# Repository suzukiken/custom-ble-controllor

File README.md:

# Xiao BLE Controller

Seeed XIAO 向けのファーム／周辺ツール集です。**スタック（どの MCU・どのランタイムか）で場所が分かれています。**

## ファームの場所（まずここ）

| 種類 | 置き場 | 例 |
| --- | --- | --- |
| **ZMK（XIAO nRF52840）** | リポジトリ直下 `config/` + `boards/shields/` | `sleep_xiao`, `onekey_xiao`, … |
| **Arduino（XIAO RP2040）** | [`arduino/xiao-rp2040/`](arduino/xiao-rp2040/) | `virtual-finger`（nRF を押す仮想指） |

積み重ね（nRF + RP2040）のペア:

| ZMK shield（nRF・電池） | RP2040 finger（USB） |
| --- | --- |
| `sleep_xiao`（deep sleep **あり**） | [`virtual-finger`](arduino/xiao-rp2040/virtual-finger/)（D0） |
| `sleep_xiao_pi`（同上 + Pi/BlueZ 向け BLE） | 同じ |
| `awake_xiao`（deep sleep **なし**） | 同じ |
| `awake_xiao_pi`（awake + Pi/BlueZ 向け BLE） | 同じ |

RP2040: **D0** を約5分おきにパルス。nRF は `time: …, power=…, mode=…` を打つ。

### スリープあり／なし比較（手元の機材向け）

公平に見るには **打鍵周期を同じにして sleep だけ変える**。

| 役割 | nRF ファーム | RP2040 | ホスト例 | 見るもの |
| --- | --- | --- | --- | --- |
| A | `sleep_xiao`（deep sleep **あり**） | `virtual-finger` | iPad | 持ち時間 |
| B | `awake_xiao`（deep sleep **なし**） | `virtual-finger` | iPhone | 持ち時間 |
| C | `sleep_xiao`（deep sleep あり） | **なし**（接続だけ） | Mac | ベースライン |

- 電池3本は満充電から開始。nRF=LiPo / RP2040=USB。**GND + D0** を共有。
- ホストはどれも近く・同じ部屋に固定（距離差で再送が増えると壊れる）。
- 画面は自動ロック「しない」、試験中は寝かさない。
- Notes 等に約5分ごと `time: …, power=…, mode=sleep|awake` が出る。
- 切れ時刻か、最後の `time:` で比較。A≪B なら sleep が効いている。A≈B なら接続維持が支配的。
- C が A より大幅に長いなら「5分打鍵＋起床」のコストが見える。

詳細は [`arduino/README.md`](arduino/README.md)。ZMK は user-config の都合でルートに残しています。

---

## ZMK user config（nRF52840）

Board は `xiao_ble//zmk`。ZMK 本体は [`config/west.yml`](config/west.yml) で commit `268b1b1e82150460f00fd701bcd08583d5c75d29` に固定しています。

## Shield 一覧

| Shield | ハードウェア | ピン | キーマップ / センサ |
| --- | --- | --- | --- |
| `onekey_xiao` | `one-key` | D0 ↔ GND | `SPACE` |
| `key_xiao` | `main-board` + `key-board`（PH 2） | D0 ↔ GND | `SPACE` |
| `encoder_xiao` | `main-board` + `encoder-board`（PH 3） | D1=A, D2=B, GND=C | 回転: `C_VOL_UP` / `C_VOL_DN` |
| `push_encoder_xiao` | `main-board` + `push-encoder-board`（PH 4） | D7=A, D6=B, D5=SW, GND=C | Push: `C_MUTE` / 回転: 音量 |
| `fourway_xiao` | `main-board-8` + `4way-re-board`（8ピン, RKJXT1F42001） | 下表 | 十字・Enter・音量 |
| `key_encoder_xiao` | Xiao + keyswitch + encoder 一体 | D0=SW / D1=A, D2=B, GND | `SPACE` + 方向キー上下 |
| `rkjxt_xiao` | Xiao + RKJXT1F42001 一体 | 下表 | 十字・Enter・音量 |
| `sleep_xiao` | 仮想指 + deep sleep あり | D0 ↔ RP2040 | D0=status |
| `sleep_xiao_pi` | `sleep_xiao` + Raspberry Pi/BlueZ 向け BLE | 同上 | 2M PHY 無効など |
| `awake_xiao` | 仮想指 + deep sleep **なし** | D0 ↔ RP2040 | D0=status |
| `awake_xiao_pi` | `awake_xiao` + Pi/BlueZ 向け BLE | 同上 | 接続切り分け用 |
| `drain_xiao` | **電池消費最大化**（充電電流計測の前処理） | （キー不要） | RGB+CPU+HID spam |
| `powerbtn_xiao` | 電源ボタン（ZMK Soft Off） | D0 ↔ GND | 3秒長押しで System OFF / 押して起動 |

BLE 名はそれぞれ `OneKey Xiao` / `Key Xiao` / `Encoder Xiao` / `PushEnc Xiao` / `Fourway Xiao` / `KeyEnc Xiao` / `Rkjxt Xiao` / `Sleep Xiao` / `Sleep Pi Xiao` / `Awake Xiao` / `Awake Pi Xiao` / `Drain Xiao` / `PowerBtn Xiao` です（ZMK の上限は15文字）。

status の周期は nRF 側ではなく **RP2040**（既定 5 分）が決めます。

共通設定（各 `config/*.conf`）:

- `CONFIG_ZMK_BLE=y` / `CONFIG_ZMK_USB=n`
- `sleep_xiao`: `CONFIG_ZMK_SLEEP=y` / `CONFIG_ZMK_IDLE_SLEEP_TIMEOUT=20000`（status 打鍵後に寝る余裕）。`powerbtn_xiao` と `awake_xiao` は `CONFIG_ZMK_SLEEP=n`
- エンコーダ付きは `CONFIG_EC11=y`

## 配線

### onekey_xiao / key_xiao

```text
XIAO D0 ----[ switch ]---- XIAO GND
```

`zmk,kscan-gpio-direct`、`GPIO_ACTIVE_LOW | GPIO_PULL_UP`。

### encoder_xiao

```text
XIAO D1 ---- Encoder A
XIAO D2 ---- Encoder B
XIAO GND --- Encoder C
```

キー入力は使わず（overlay 上の D10 は未使用スタブ）、回転のみ。

### key_encoder_xiao

Xiao・キースイッチ・ロータリーエンコーダ（プッシュなし）を1枚に載せた構成です。

```text
XIAO D0  ---- keyswitch pin1
XIAO GND ---- keyswitch pin2

XIAO D1  ---- encoder pin1 (A)
XIAO D2  ---- encoder pin3 (B)
XIAO GND ---- encoder pin2 (C)
```

キーは `SPACE`、回転は方向キー Up/Down です。

### push_encoder_xiao

```text
XIAO D7 ---- Encoder A
XIAO D6 ---- Encoder B
XIAO D5 ---- SW (Push)
XIAO GND --- Encoder C
```

### fourway_xiao（RKJXT1F42001）

```text
XIAO D4 ---- A      → UP
XIAO D0 ---- B      → RIGHT
XIAO D2 ---- C      → DOWN
XIAO D3 ---- D      → LEFT
XIAO D5 ---- Push   → ENTER
XIAO D6 ---- Encoder A
XIAO D1 ---- Encoder B
XIAO GND --- GND (Com / ECom)
```

keymap の並びは A, B, C, D, Push。回転は `C_VOL_UP` / `C_VOL_DN`（`steps = 20`）。

### rkjxt_xiao

Xiao と RKJXT1F42001 を1枚に載せた構成です。

```text
XIAO D4 ---- A      → UP
XIAO D0 ---- B      → RIGHT
XIAO D2 ---- C      → DOWN
XIAO D3 ---- D      → LEFT
XIAO D5 ---- Push   → (無効 / 方向と同時導通のため)
XIAO D6 ---- EA (Encoder A)
XIAO D1 ---- EB (Encoder B)
XIAO GND --- GND
```

keymap の並びは A, B, C, D, Push。回転は音量 Up/Down（`steps = 20`）。

RKJXT1F42001 は方向入力時に Push も同時に落ちるため、`rkjxt_xiao` では Push を `&none` にしています（Enter が乗らないようにするため）。中央プッシュが必要なら別途相談してください。

### powerbtn_xiao

```text
XIAO D0 ----[ switch ]---- XIAO GND
```

`zmk,kscan-gpio-direct`。短押しではキーは出ず、3秒長押しで Soft Off（後述）。

### sleep_xiao / awake_xiao（仮想指 + status）

目的は「BLE 接続したまま、約5分に1回 status 行を打つ」ときの持ち時間の見積もりです。`sleep_xiao` は deep sleep あり、`awake_xiao` はなし。

```text
nRF D0 ---- RP2040 D0   (status trigger, ~5min)
nRF GND --- RP2040 GND
```

- D0: keymap は `&none`。`soak_status` が `time: …, power=…, mode=…` + Enter を打つ
- `sleep_xiao`: 入力後 **20秒** でスリープ（status 打鍵が終わる余裕）
- status 周期は **RP2040** 側（既定 5 分）。deep sleep 中でも D0 で起きて送信できる

#### 実験のやり方

1. LiPo を nRF の BAT に接続し、この uf2 を書く
2. ホストと `Sleep Xiao` / `Awake Xiao` をペアリングし、Notes 等を開く
3. RP2040 を積み、**GND + D0** を共有（3V3/5V/BAT は繋がない）。RP2040 は USB 電源
4. 約5分ごとに Notes に status 行が出ることを確認し、電池切れまで測る

見積もりの目安: `稼働時間 = 満充電から不能になるまでの時間`。最後の `time:` でも比較できます。

### sleep_xiao_pi（Raspberry Pi / BlueZ 向け）

`sleep_xiao` と同じ打鍵・スリープ構成で、**BLE だけ** Linux（特に Raspberry Pi の BlueZ）向けに変えています。

ログに `le-connection-abort-by-local` と `Connected: yes`/`no` の高速点滅が出る場合、多くは次のどちらかです。

1. **Pi 側がリンクを切っている**（2M PHY 交渉や SMP/ボンディング不整合で BlueZ が abort）
2. **片方だけの古いボンド**（iPhone 等とペアした鍵が残り、Pi が同じアドレスに古い鍵で接続しようとして失敗→再試行ループ）

`sleep_xiao_pi` では主に次を入れています。

- `CONFIG_ZMK_BLE_EXPERIMENTAL_CONN=y` / `CONFIG_BT_CTLR_PHY_2M=n`（2M PHY 無効）
- ボンド上書き許可（再ペアしやすくする）
- `CONFIG_BT_GATT_ENFORCE_SUBSCRIPTION=n`
- idle sleep を **10分**（virtual-finger の5分より長くする）。あわせて idle も5分に延長
- 送信出力 `CONFIG_BT_CTLR_TX_PWR_PLUS_8=y`

初回は両方きれいにしてからペアしてください。

1. nRF にいったん `settings_reset` を書き、すぐ `sleep_xiao_pi` を書き直す
2. Pi: `bluetoothctl remove <addr>`（該当デバイス）、必要なら `sudo systemctl restart bluetooth`
3. デバイスを起こした状態（D0 パルス後〜60秒以内）で次を実行

```text
agent off
agent NoInputNoOutput
default-agent
scan on
pair <addr>
trust <addr>
connect <addr>
```

**重要:** デスクトップ GUI に「Enter Code 2314134」のような表示が出ることがあります。これは「キーボードでパスコードを打て」という意味で、数字キーの無い本機では入力できません。**GUI のダイアログはキャンセル**し、上記のとおり `agent NoInputNoOutput` の bluetoothctl だけでペアしてください（Just Works）。GUI エージェントが割り込むと失敗しやすいです。

#### つながらないときの切り分け

ログの `Connected: yes`/`no` 連打 + `le-connection-abort-by-local` は、だいたい次の合成です。

1. **ペア未完了／壊れたボンド**（GUI パスコードをキャンセルしたあとに特に多い。`trust` だけでは足りない）
2. **BlueZ × ZMK HID** の相性（2M PHY・認証。ファーム側は 2M 無効などを入れ済み）
3. **deep sleep**（広告が止まる／再接続のたびに同じ失敗を繰り返す）

先に **`awake_xiao_pi`（BLE名 `Awake Pi Xiao`）** でペアを試してください。deep sleep なし・同じ BLE 対策です。

- `awake_xiao_pi` で安定する → 問題は主に sleep／再接続。そのボンドのまま `sleep_xiao_pi` へ載せ替えを検討
- `awake_xiao_pi` でも同じ → deep sleep ではなく **Pi/BlueZ 側**（ボンド掃除・agent・場合によって BT ドングル／OS）が本丸

そのとき `info <addr>` で `Paired: yes` か、できれば `sudo btmon` の切断理由（Authentication / Timeout 等）を見ると次が決まります。

## virtual-finger（Arduino RP2040）

置き場: [`arduino/xiao-rp2040/virtual-finger/`](arduino/xiao-rp2040/virtual-finger/)

| ピン | 周期（既定） | nRF 側の意味 |
| --- | --- | --- |
| `D0` | 5分 | status トリガ（`soak_status`） |

**1.5秒** LOW パルス（deep sleep 起床＋スキャン検出用）。パルス時は赤 LED。起動後約15秒で最初の status が出ます。

GitHub Actions [`Build Arduino RP2040 virtual-finger`](.github/workflows/build-arduino-rp2040-virtual-finger.yml) が UF2 を出します。

1. Actions の Artifacts から `arduino-rp2040-virtual-finger` をダウンロード
2. XIAO RP2040 で **B を押しながら R**（または B 押しながら挿す）→ `RPI-RP2` ドライブ
3. `xiao-rp2040-virtual-finger.uf2` をドラッグ&ドロップ

周期は `INTERVAL_MS` で変更できます。

## drain_xiao（電池を早く減らす・充電計測の前処理）

40mAh などで **半分付近まで落としてから充電電流を測る**ための、消費最大化ファームです。

| 項目 | 内容 |
| --- | --- |
| BLE 名 | `Drain Xiao` |
| sleep | **なし** |
| 動作 | RGB 全点灯 + CPU busy + 約40msおき HID（`RIGHT`）+ 約30秒ごと `time/power` 行（末尾改行） |
| TX | `CONFIG_BT_CTLR_TX_PWR_PLUS_8` |

### 使い方

1. LiPo のみ（USB 給電だと電池が減らない／計測が崩れる）
2. `Drain Xiao` をホストにペアし、Notes 等を開く（HID spam と status 用）
3. 約30秒ごと `time: …, power=XX, mode=drain` を見る
4. **`power` がだいたい 50 前後**になったら止める（抜く／別ファームへ）
5. その状態で充電開始し、電流を測る

注意: 放置すると空近くまで減る可能性があります。50%狙いなら `power=` を見て止めてください。

## 電源ボタン（Soft Off）

D0–GND のスイッチで nRF52840 の **System OFF**（ZMK Soft Off）を入切します。短押しではキーは出ません。

| 操作 | 動作 |
| --- | --- |
| Soft Off 中に押す | ON（即起動） |
| ON 中に **3秒長押し** → 離す | Soft Off |

```text
XIAO D0 ----[ switch ]---- XIAO GND
```

- Shield: `powerbtn_xiao`（他 shield と同じ ZMK ビルド）
- アイドルスリープなし（OFF するまで ON のまま）
- LED 演出や「1秒長押しで ON 確定」はなし

## ビルド

[`build.yaml`](build.yaml) の全 shield が GitHub Actions（`Build ZMK firmware`）でビルドされます。

```yaml
include:
  - board: xiao_ble//zmk
    shield: onekey_xiao
  - board: xiao_ble//zmk
    shield: key_xiao
  - board: xiao_ble//zmk
    shield: encoder_xiao
  - board: xiao_ble//zmk
    shield: push_encoder_xiao
  - board: xiao_ble//zmk
    shield: fourway_xiao
  - board: xiao_ble//zmk
    shield: key_encoder_xiao
  - board: xiao_ble//zmk
    shield: rkjxt_xiao
  - board: xiao_ble//zmk
    shield: sleep_xiao
  - board: xiao_ble//zmk
    shield: sleep_xiao_pi
  - board: xiao_ble//zmk
    shield: awake_xiao
  - board: xiao_ble//zmk
    shield: awake_xiao_pi
  - board: xiao_ble//zmk
    shield: drain_xiao
  - board: xiao_ble//zmk
    shield: powerbtn_xiao
  - board: xiao_ble//zmk
    shield: settings_reset
```

成果物（Artifacts の `firmware`）:

- `onekey_xiao-xiao_ble__zmk-zmk.uf2`
- `key_xiao-xiao_ble__zmk-zmk.uf2`
- `encoder_xiao-xiao_ble__zmk-zmk.uf2`
- `push_encoder_xiao-xiao_ble__zmk-zmk.uf2`
- `fourway_xiao-xiao_ble__zmk-zmk.uf2`
- `key_encoder_xiao-xiao_ble__zmk-zmk.uf2`
- `rkjxt_xiao-xiao_ble__zmk-zmk.uf2`
- `sleep_xiao-xiao_ble__zmk-zmk.uf2`
- `sleep_xiao_pi-xiao_ble__zmk-zmk.uf2`
- `awake_xiao-xiao_ble__zmk-zmk.uf2`
- `awake_xiao_pi-xiao_ble__zmk-zmk.uf2`
- `drain_xiao-xiao_ble__zmk-zmk.uf2`
- `powerbtn_xiao-xiao_ble__zmk-zmk.uf2`
- `settings_reset-xiao_ble__zmk-zmk.uf2`（BLE ペアリング復旧用）

### UF2 書き込み

1. XIAO を USB-C 接続
2. `RST` を素早く2回 → ブートローダー
3. マウントされたドライブへ `.uf2` をコピー

### ペアリング

OS の Bluetooth 設定で上記 BLE 名を選択。`BT_CLR` 等は未割り当てなので、付け直すときは `settings_reset` ファームを使うか、後から制御キーを追加してください。

## 変更箇所

| 目的 | ファイル |
| --- | --- |
| キーコード・音量など | `config/<shield>.keymap` |
| ピン割り当て | `boards/shields/<shield>/<shield>.overlay` |
| BLE / sleep / EC11 | `config/<shield>.conf` |
| ビルド対象 | `build.yaml` |

回転方向が逆のときは、該当 overlay の `a-gpios` と `b-gpios` を入れ替えます。

## ファイル構成

```text
.
├── .github/workflows/
│   ├── build.yml                                      # ZMK (nRF)
│   └── build-arduino-rp2040-virtual-finger.yml        # Arduino RP2040
├── arduino/
│   ├── README.md
│   └── xiao-rp2040/
│       └── virtual-finger/               # ↔ ZMK sleep_xiao / awake_xiao
├── config/                               # ZMK conf / keymap / west.yml
├── boards/shields/                       # ZMK shields
├── src/soak_status.c                     # D0 トリガで time/power HID
├── src/power_drain.c                     # 消費最大化（drain_xiao）
├── build.yaml
├── CMakeLists.txt / Kconfig / zephyr/    # ZMK extra module
├── pcb/
└── 3d/
```

Gerber（`*.gbr`）・ドリル（`*.drl`）・`*.kicad_prl` / `fp-info-cache` / `.history/` は `.gitignore` 対象です。

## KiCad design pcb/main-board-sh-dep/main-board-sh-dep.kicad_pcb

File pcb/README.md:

# map-controllor PCB (KiCad)

Seeed XIAO RP2040 (U1) と Alps RKJXT1F42001 (SW1) を載せる基板データです。

基板設計の仕様（製造制約・配線ルール・配線案）は [`AGENTS.md`](AGENTS.md) を参照してください。
AI エージェントに設計を任せる場合は、まず `AGENTS.md` を読ませてください。

## 構成

## 結線

| SW1 (RKJXT1F42001) | ネット | U1 (XIAO RP2040) |
| --- | --- | --- |

スイッチ・エンコーダの共通端子はすべて GND に落とし、
RP2040 の内蔵プルアップ(QMK の direct pins / encoder デフォルト)で読む。
外付け部品は不要。

## ファイル

- `encoder.kicad_pro` / `encoder.kicad_pcb` — KiCad 10 プロジェクト
- `footpritn/footpritn.pretty/` — XIAO RP2040 と RKJXT1F42001 のフットプリント
- `scripts/` — 配線・検証に使った pcbnew スクリプト
- `render_top.png` / `render_bottom.png` — レンダリング画像

## 検証

```bash
/Applications/KiCad/KiCad.app/Contents/MacOS/kicad-cli pcb drc encoder.kicad_pcb
```

エラー0件・未結線0件(シルクとマスクの重なり警告のみ)。

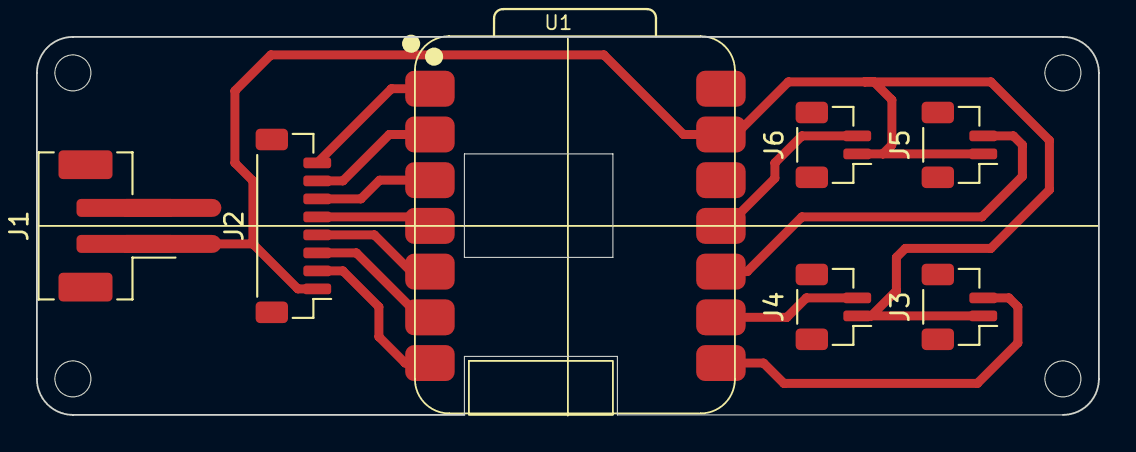
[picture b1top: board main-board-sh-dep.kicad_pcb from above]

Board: 2 copper layers, 59.0 x 21.0 mm, 7 parts (0 on the bottom side), 12 nets.

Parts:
J1: Conn_01x02; JST_PH_B2B-PH-SM4-TB_1x02-1MP_P2.00mm_Vertical
J2: Conn_01x08; JST_SH_BM08B-SRSS-TB_1x08-1MP_P1.00mm_Vertical
J3, J4, J5, J6: Conn_01x02; JST_SH_BM02B-SRSS-TB_1x02-1MP_P1.00mm_Vertical
U1: XIAO-nRF52840-SMD_NC

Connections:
GND: J1.1, J2.1, J3.1, J4.1, J5.1, J6.1, U1.13 (GND)
unnamed: J2.2, U1.7 (GP6)
unnamed: J2.3, U1.6 (GP5)
unnamed: J2.4, U1.5 (GP4)
unnamed: J2.5, U1.4 (GP3)
unnamed: J2.6, U1.3 (GP2)
unnamed: J2.7, U1.2 (GP1)
unnamed: J2.8, U1.1 (GP0)
unnamed: J3.2, U1.8 (GP7)
unnamed: J4.2, U1.9 (GP8)
unnamed: J5.2, U1.10 (GP9)
unnamed: J6.2, U1.11 (GP10)
